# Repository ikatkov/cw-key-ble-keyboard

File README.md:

# Morse Code Keyer BLE

## Overview
This project is a Bluetooth keyboard for a Morse Code keyer. 

Main purpose is to practice morse code in the Morse Mania iOS app with a real morse code key.

Data flow looks like this

a CW Keyer -over audio-wire-> this BT Keyboard box --over BT-> iPhone

The Morse Mania app expect "[" and "]" buttons, so this Bluetooth keyboard sends key_down and key_up events.

### Battery level
On iOS battery level is visible in Battery widget - Swipe right on the Home Screen to access the Today View.
### Multiple languages
If you have more than one language installed, you must switch to "English" before this BT keyboard connects. If you don't the Morse Mania app would be gettting whatever your national symbols are mapped to the "[" and "]" buttons on the standard keyboard and the app would looks broken.

### Key repeat
You might want to disable auto-key repeat in iOS Settings > Accessibility > Keyboards

## Features
- BLE keyboard functionality
- Tone generation for startup and shutdown
- Voltage detection to monitor battery status, audio bips when voltage is below ~2.9V
- Inactivity 5min auto turn-off

## Usage
- Connect the Arduino to your computer and upload the code.
- Open a BLE-capable device and connect to the "Morse Code Keyer".
- Use the iambic CW paddles to send Morse code.

## Assembly

See schematic and PCB in the  "kicad" folder.
The firmware in the "firmware" folder.

[See interactive PCB 3d view here](https://3dviewer.net/#model=https://github.com/ikatkov/cw-key-ble-keyboard/main/pcb.wrl)

## Acknowledgments
- [Arduino](https://www.arduino.cc/)
- [BleKeyboard Library](https://github.com/Teckel12/BLEKeyboard)

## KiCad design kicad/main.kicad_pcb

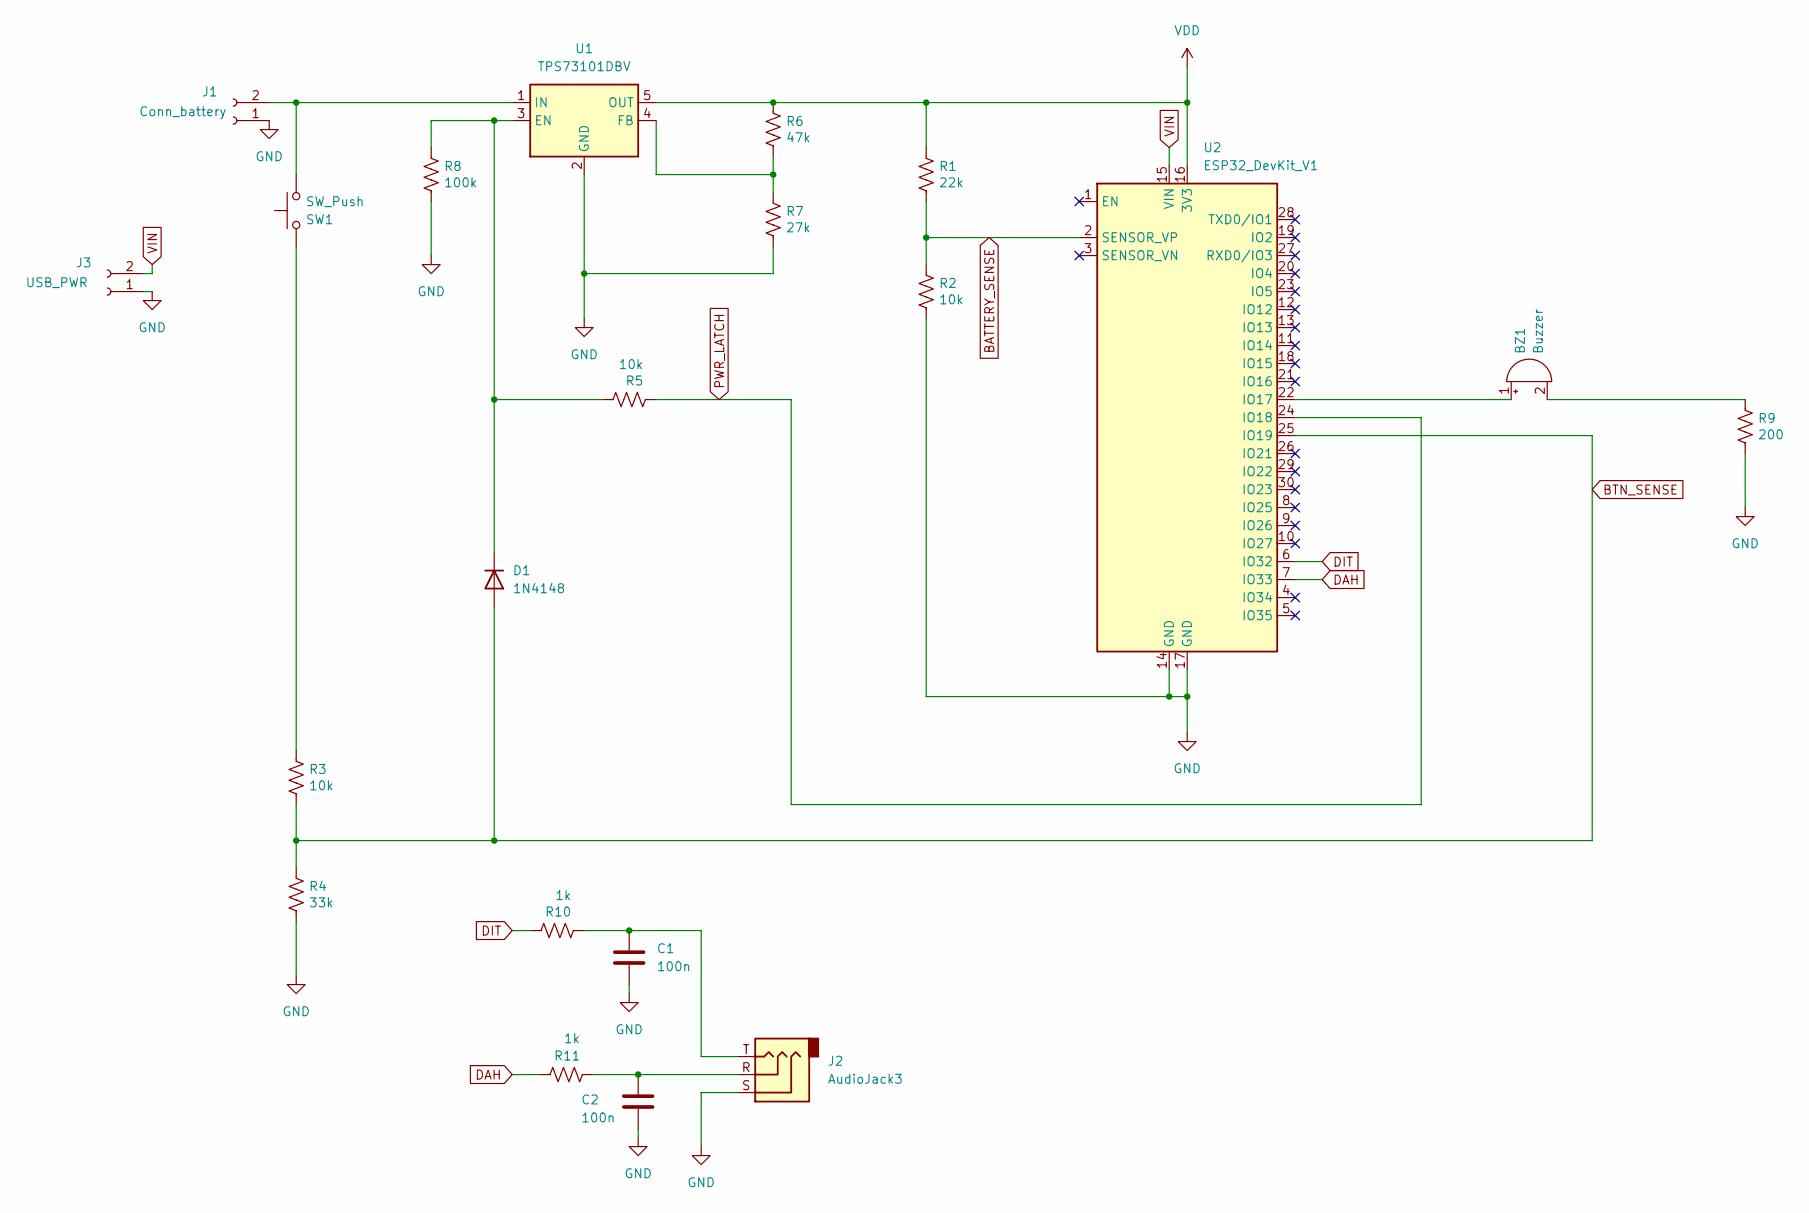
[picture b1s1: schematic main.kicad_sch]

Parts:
BZ1: Buzzer; Buzzer-GT-0905A
C1, C2: 100n; C_1206_3216Metric
D1: 1N4148; D_MELF
J1: Conn_battery; SolderWire-1.5sqmm_1x02_P6mm_D1.7mm_OD3mm
J2: AudioJack3; Jack_3.5mm_CUI_SJ1-3535NG_Horizontal
J3: USB_PWR; SolderWire-1.5sqmm_1x02_P6mm_D1.7mm_OD3mm
R1: 22k; R_0805_2012Metric
R2, R3, R5: 10k; R_0805_2012Metric
R4: 33k; R_0805_2012Metric
R6: 47k; R_0805_2012Metric
R7: 27k; R_0805_2012Metric
R8: 100k; R_0805_2012Metric
R9: 200; R_0805_2012Metric
R10, R11: 1k; R_0805_2012Metric
SW1: SW_Push; SW_PUSH_6mm
U1: TPS73101DBV; SOT-23-5
U2: ESP32_DevKit_V1; esp32_devkit_v1_doit

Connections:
BATTERY_SENSE: R1.2, R2.1, U2.2 (SENSOR_VP)
BTN_SENSE: D1.2 (A), R3.2, R4.1, U2.25 (IO19)
DAH: R11.1, U2.7 (IO33)
DIT: R10.1, U2.6 (IO32)
GND: C1.2, C2.2, J1.1, J2.S, J3.1, R2.2, R4.2, R7.2, R8.2, R9.2, U1.2 (GND), U2.14 (GND), U2.17 (GND)
unnamed: BZ1.1 (+), U2.22 (IO17)
unnamed: BZ1.2 (-), R9.1
unnamed: C1.1, J2.T, R10.2
unnamed: C2.1, J2.R, R11.2
unnamed: D1.1 (K), R5.1, R8.1, U1.3 (EN)
unnamed: J1.2, SW1.1, U1.1 (IN)
unnamed: R3.1, SW1.2
unnamed: R6.2, R7.1, U1.4 (FB)
PWR_LATCH: R5.2, U2.24 (IO18)
VDD: R1.1, R6.1, U1.5 (OUT), U2.16 (3V3)
VIN: J3.2, U2.15 (VIN)

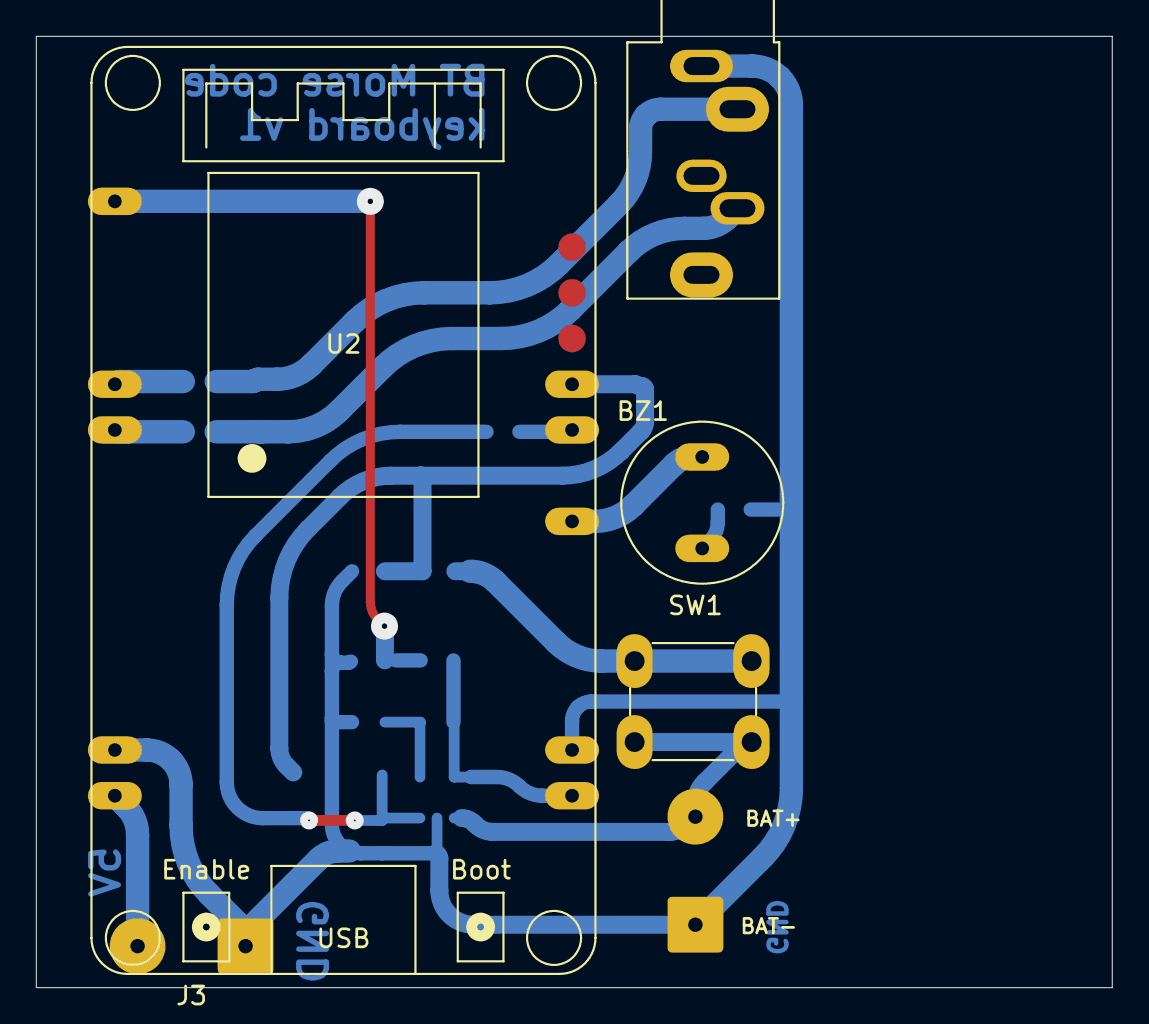
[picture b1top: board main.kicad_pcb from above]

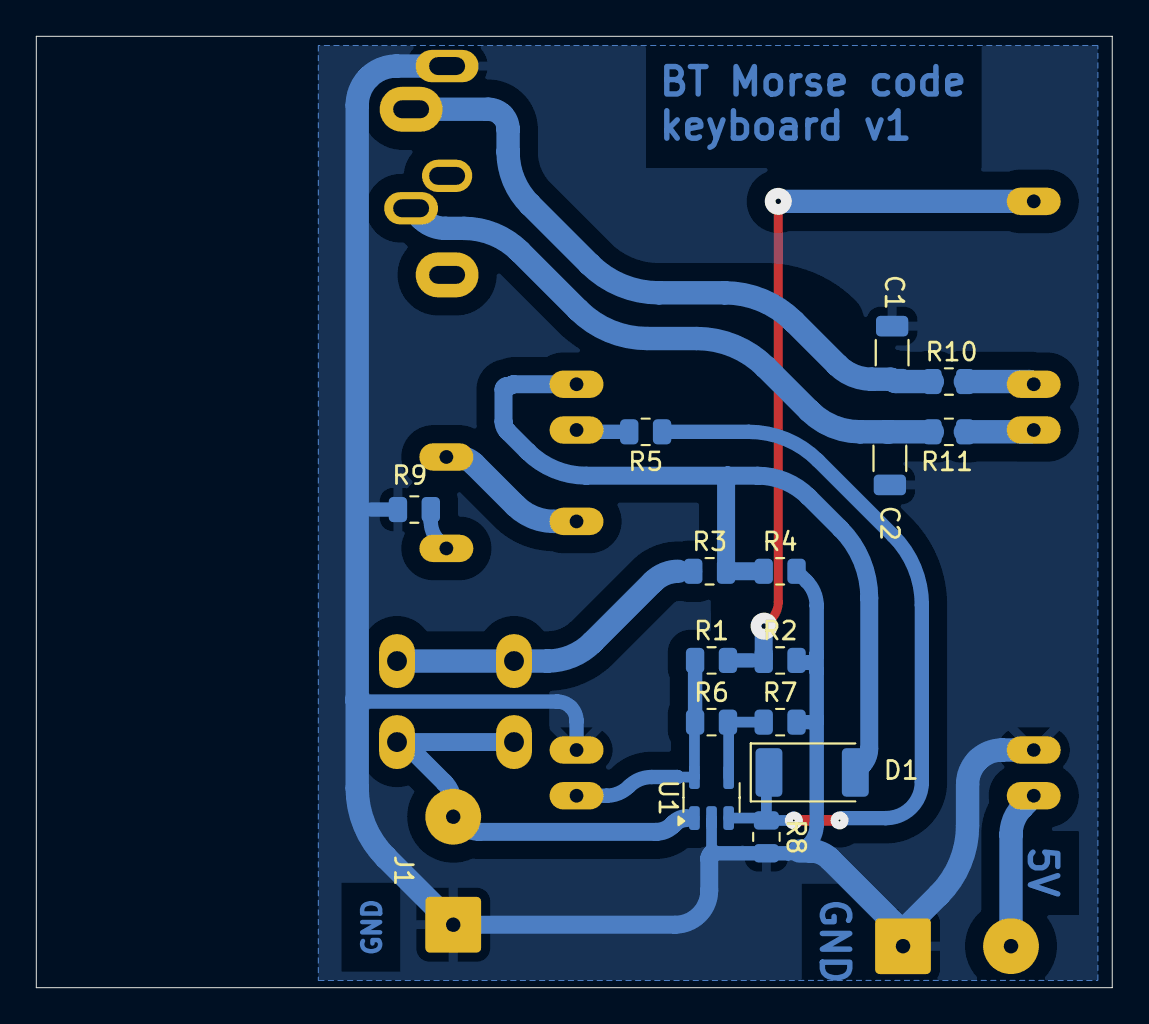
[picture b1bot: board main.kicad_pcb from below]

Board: 4 copper layers, 59.8 x 52.9 mm, 21 parts (16 on the bottom side), 16 nets.

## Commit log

2024-12-11 feat: basic keyboard
2024-12-11 fix: dependency
2024-12-11 feat: add buttons support
2024-12-15 moved files and update firmware
2024-12-16 feat: schematic, pcb layout, code, enclosure
2024-12-16 docs: add 3d images and 3d models
2024-12-16 docs: add readme
2024-12-19 doc: Update readme
2024-12-21 feat: update schematic with protection RC
2024-12-21 doc: instructions on how to disable keyboard repeat in iOS, add battery indicator to BLE
